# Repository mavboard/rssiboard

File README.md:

rssiboard
=========

This tiny board can convert PWM-based RSSI signals (such as those produced by the RSSI ports on FrSky Rx modules) into an analog signal. This is very useful if your flight controller only understands analog RSSI, such as the APM 2.x.

It's a simple but very useful board that connects easily. For APM 2.x, simply connect the PWM side to the RSSI port on your receiver, and the other to an analog port on the APM, and enable RSSI in the mission planner!

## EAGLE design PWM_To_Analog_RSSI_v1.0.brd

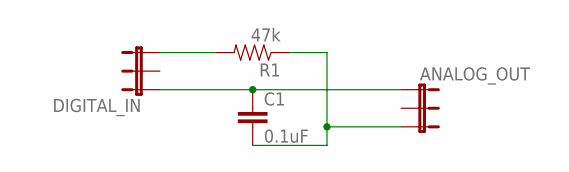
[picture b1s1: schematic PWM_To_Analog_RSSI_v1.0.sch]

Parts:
ANALOG_OUT: JUMPER-3PTH; 1X03
C1: 0.1uF; CAP-PTH-SMALL
DIGITAL_IN: JUMPER-3PTH; 1X03
R1: 47k; AXIAL-0.3-KIT

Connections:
ANALOG: ANALOG_OUT.3, C1.2, R1.P$1 (1)
GND: ANALOG_OUT.1, C1.1, DIGITAL_IN.1
PWM: DIGITAL_IN.3, R1.P$2 (2)

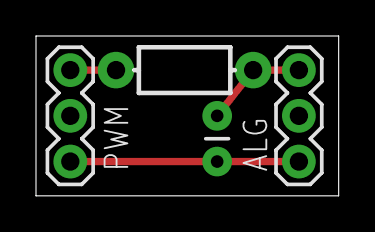
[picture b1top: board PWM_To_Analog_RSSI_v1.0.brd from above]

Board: 2 copper layers, 16.8 x 8.9 mm, 4 parts (0 on the bottom side), 3 nets.

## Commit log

2014-04-29 Initial import
2014-04-29 fix image

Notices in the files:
parts and their libraries:
SparkFun-Passives: Licensing: CC v3.0 Share-Alike You are welcome to use this library for commercial purposes.
